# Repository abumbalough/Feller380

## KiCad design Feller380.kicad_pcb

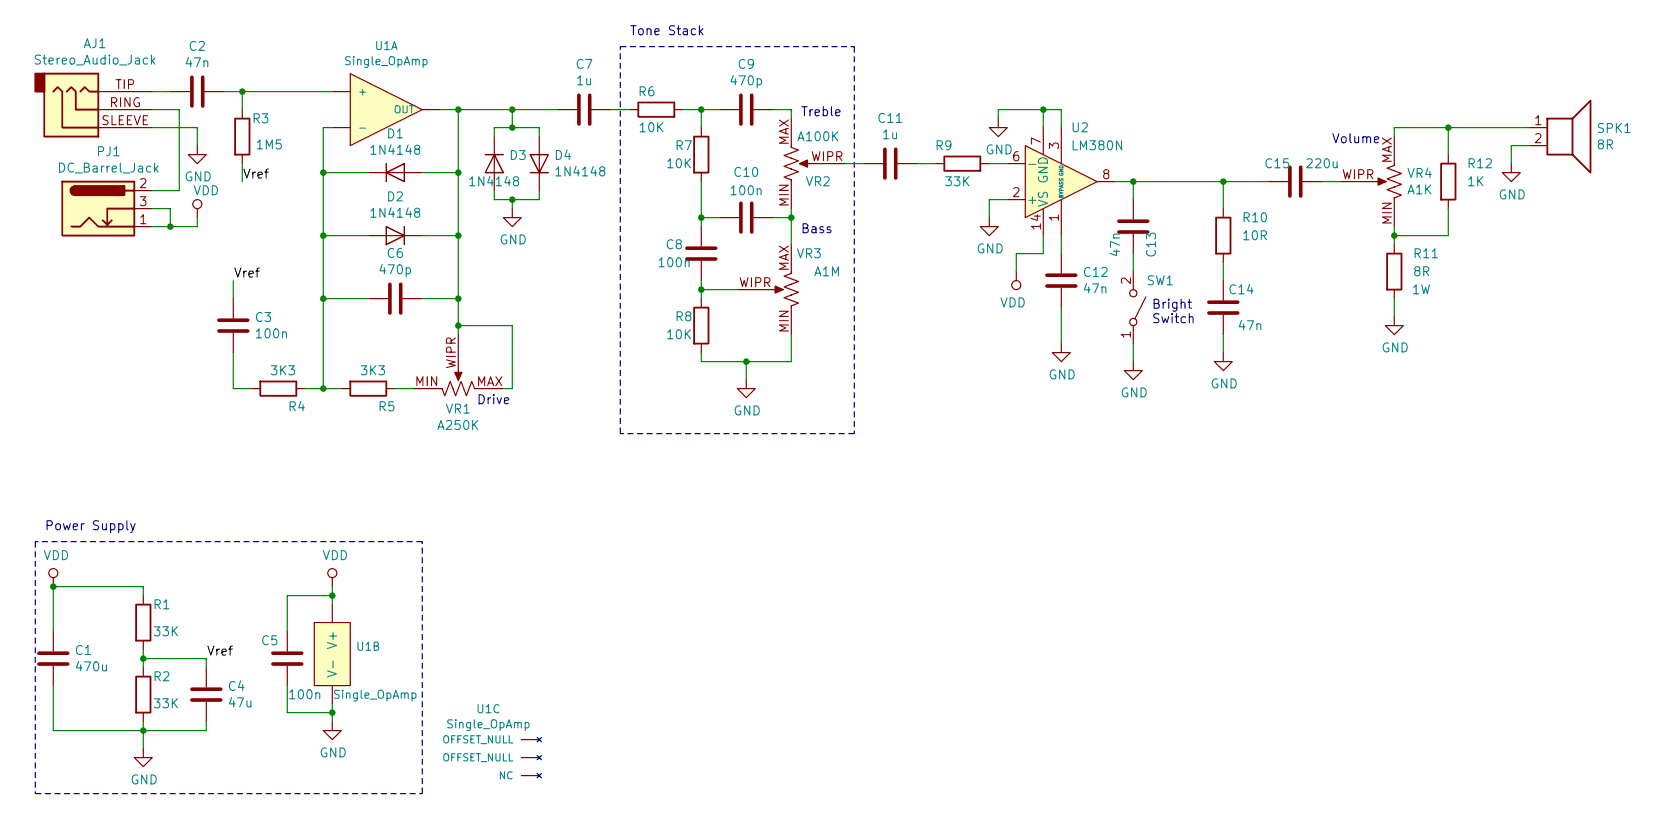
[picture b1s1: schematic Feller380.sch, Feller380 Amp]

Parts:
AJ1: Stereo_Audio_Jack
C1: 470u; C_Radial_D5.0mm_H5.0mm_P2.00mm
C2, C12, C13, C14: 47n; C_Rect_L7.2mm_W5.5mm_P5.00mm_FKS2_FKP2_MKS2_MKP2
C3, C8, C10: 100n; C_Rect_L7.2mm_W5.5mm_P5.00mm_FKS2_FKP2_MKS2_MKP2
C4: 47u; C_Radial_D5.0mm_H5.0mm_P2.00mm
C5: 100n; C_Disc_D3.8mm_W2.6mm_P2.50mm
C6, C9: 470p; C_Rect_L7.2mm_W5.5mm_P5.00mm_FKS2_FKP2_MKS2_MKP2
C7, C11: 1u; C_Rect_L7.2mm_W5.5mm_P5.00mm_FKS2_FKP2_MKS2_MKP2
C15: 220u; C_Radial_D5.0mm_H5.0mm_P2.00mm
D1, D2, D3, D4: 1N4148; Diode_Socket
PJ1: DC_Barrel_Jack
R1, R2, R9: 33K; R_Axial_DIN0207_L6.3mm_D2.5mm_P7.62mm_Horizontal
R3: 1M5; R_Axial_DIN0207_L6.3mm_D2.5mm_P7.62mm_Horizontal
R4, R5: 3K3; R_Axial_DIN0207_L6.3mm_D2.5mm_P7.62mm_Horizontal
R6, R7, R8: 10K; R_Axial_DIN0207_L6.3mm_D2.5mm_P7.62mm_Horizontal
R10: 10R; R_Axial_DIN0207_L6.3mm_D2.5mm_P7.62mm_Horizontal
R11: 8R; R_Axial_DIN0207_L6.3mm_D2.5mm_P7.62mm_Horizontal
R12: 1K; R_Axial_DIN0207_L6.3mm_D2.5mm_P7.62mm_Horizontal
SPK1: 8R; SolderWirePad_1x02_P3.81mm_Drill0.8mm
SW1: SW_SPST; SolderWirePad_1x02_P3.81mm_Drill0.8mm
U1: Single_OpAmp; DIP-8_Socket
U2: LM380N; DIP-14_W7.62mm_Socket
VR1: A250K; Pot
VR2: A100K; Pot
VR3: A1M; Pot
VR4: A1K; Pot

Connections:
/Vref: C3.2, C4.2, R1.2, R2.1, R3.2
GND: AJ1.SLEEVE, C1.1, C4.1, C5.1, C12.1, C14.2, D3.2 (A), D4.1 (K), R2.2, R8.2, R11.2, SPK1.2, SW1.1 (A), U1.4 (V-), U2.2 (+), U2.3 (GND), U2.4 (GND), U2.5 (GND), U2.7 (GND), U2.10 (GND), U2.11 (GND), U2.12 (GND), VR3.MIN
unnamed: AJ1.RING, PJ1.2 (GND)
unnamed: AJ1.TIP, C2.2
unnamed: C2.1, R3.1, U1.3 (+)
unnamed: C3.1, R4.2
unnamed: C6.1, C7.2, D1.2 (A), D2.1 (K), D3.1 (K), D4.2 (A), U1.6 (OUT), VR1.MAX, VR1.WIPR
unnamed: C6.2, D1.1 (K), D2.2 (A), R4.1, R5.2, U1.2 (-)
unnamed: C7.1, R6.1
unnamed: C8.1, R8.1, VR3.WIPR
unnamed: C9.1, VR2.MAX
unnamed: C9.2, R6.2, R7.1
unnamed: C10.1, VR2.MIN, VR3.MAX
unnamed: C8.2, C10.2, R7.2
unnamed: C11.1, R9.1
unnamed: C11.2, VR2.WIPR
unnamed: C12.2, U2.1 (BYPASS)
unnamed: C13.1, C15.2, R10.1, U2.8
unnamed: C13.2, SW1.2 (B)
unnamed: C14.1, R10.2
unnamed: C15.1, VR4.WIPR
unnamed: R5.1, VR1.MIN
unnamed: R9.2, U2.6 (-)
unnamed: R11.1, R12.2, VR4.MIN
unnamed: R12.1, SPK1.1, VR4.MAX
VDD: C1.2, C5.2, PJ1.1 (V+), PJ1.3 (SW), R1.1, U1.7 (V+), U2.14 (VS)

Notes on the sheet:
Power Supply
Drive
Volume
Bright Switch
Treble
Bass
Tone Stack

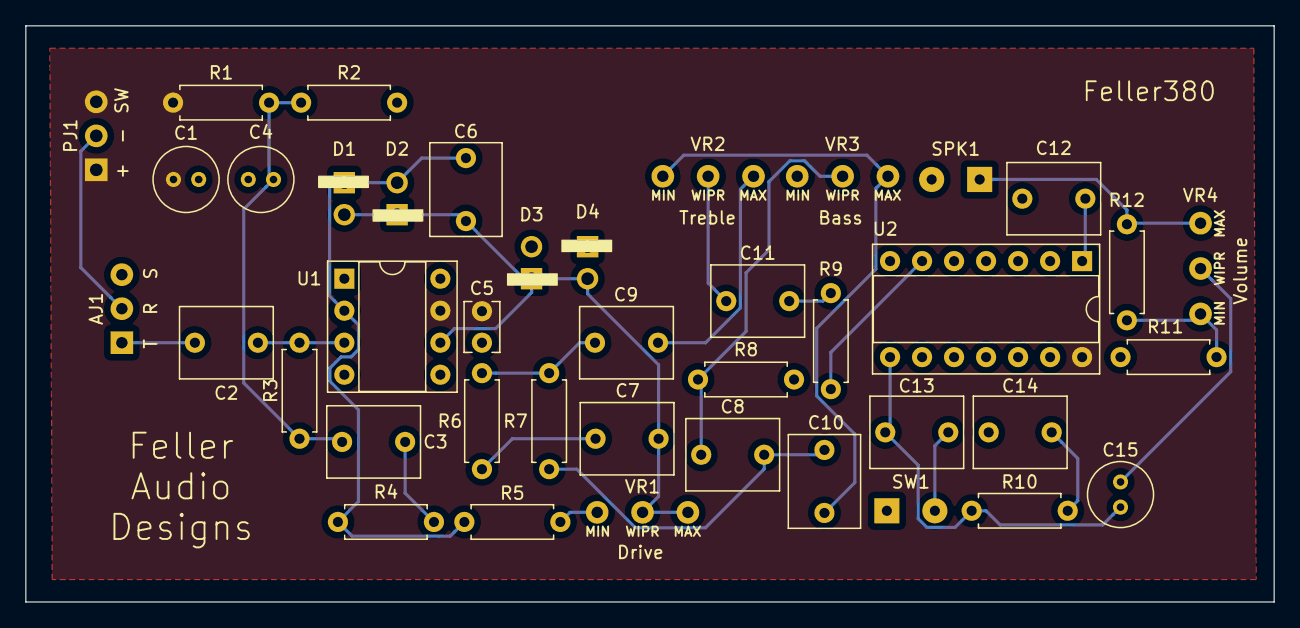
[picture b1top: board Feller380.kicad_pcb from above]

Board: 2 copper layers, 99.1 x 45.7 mm, 41 parts (0 on the bottom side), 26 nets.

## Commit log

2019-08-28 Directory initialization
